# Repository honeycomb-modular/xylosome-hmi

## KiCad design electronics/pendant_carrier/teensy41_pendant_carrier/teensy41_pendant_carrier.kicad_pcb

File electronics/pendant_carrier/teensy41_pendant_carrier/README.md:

# Teensy 4.1 Pendant Carrier — KiCad project

A 2-layer carrier board that hosts a socketed Teensy 4.1 and breaks out two
pushbuttons and one Grayhill **62AG22-H5-P** optical encoder to JST-XH
connectors. The Teensy's own micro-USB carries data + power to a Raspberry Pi;
there is no power supply circuitry on the board. The encoder and buttons are
**not** mounted to this PCB — they wire in via ribbon/JST cables.

Complete KiCad **7** project. KiCad 8/9 will open it and offer a format
upgrade — expected and safe.

## This revision: board re-shaped to Sketch10.dxf

The board outline is now built **directly from your `Sketch10.dxf`** — the tall
pendant shape, ~48.7 x 89.3 mm, with the narrow body and the right-side bump,
all 8 filleted corners. The **4 mounting holes are at the exact DXF positions**
(2 on the body centreline, 2 in the bump).

Because the board went from a 95 mm-wide horizontal layout to this narrow
vertical one, everything was re-placed:

- **Teensy U1 is vertical**, in the long narrow body, **USB at the bottom**.
- **J1 / J2 / J3 are in the right-side bump** (the ribbon-cable area), vertical.
- **Passives** sit in the gap between the Teensy's two pin rows.
- Everything fits inside the outline and clears the mounting holes — verified.

## Opening it (close the old version first)

If the previous board is still open in KiCad, **close the project**, then open
`teensy41_pendant_carrier.kicad_pro`. **Just reload — do not run F8 / "Update PCB
from Schematic"** (everything is self-contained now; F8 is what pulled in the
oversized stock footprints last time).

In the PCB editor, press **`B`** to fill the GND-pour zones.

## Routing status

The board is now **fully routed** — all 8 nets are in copper:

- The **5 signal mains** (Teensy ↔ connector for BTN1, BTN2, ENC_A, ENC_B,
  ENC_SW) run on the top copper. To get them all crossing-free on one layer,
  J2 is placed above J1 — that ordering makes the connections monotonic.
- The **encoder pull-up / filter network** (R1, R2, C1, C2), the **debounce
  caps** (C3, C4), and the **power nets** (`+5V`, `+3V3`) route on the bottom
  copper, with **9 vias** dropping from the SMD passive pads to the bottom
  layer. The bottom copper is otherwise just the GND pour.
- **GND** is the pour on both layers — press `B` in the PCB editor to fill it.

I verified the whole thing with my own tooling: schematic netlist == PCB
netlist, **all 8 nets fully connected by copper**, every pad and via inside the
board outline, zero foreign-net crossings, zero trace-over-pad, zero via
clashes, zero trace-clearance violations, zero courtyard overlaps.

**KiCad's own DRC is still the authoritative check** — I built this without a
KiCad instance to test against, so run DRC once you've opened it (and `B` to
fill the zones first). If anything's off, the schematic is the known-good
source — *Tools → Update PCB from Schematic* re-flows it.

## Files

| File | What it is |
|---|---|
| `teensy41_pendant_carrier.kicad_pro` | Project file |
| `teensy41_pendant_carrier.kicad_sch` | Schematic — fully wired, all symbols embedded |
| `teensy41_pendant_carrier.kicad_pcb` | PCB — DXF outline, placed, 5 mains routed, GND zones |
| `teensy41_pendant_carrier.pretty/` | Project footprints: Teensy socket + both JST connectors |
| `fp-lib-table` / `sym-lib-table` | Library tables |
| `Sketch10.dxf` | Your enclosure outline (the source of the board shape) |
| `design-notes.md` | Full design document (part decode, BOM, firmware) |
| `schematic-diagram.svg` | Human-readable connection diagram |

R / C use the universal `Resistor_SMD` / `Capacitor_SMD` KiCad libraries; the
Teensy socket and JST connectors are project-local; mounting holes use the
stock `MountingHole` library.

## Netlist summary  (all routed in copper)

```
+5V     U1.VIN  J3.1  C5.1
+3V3    U1.3V3  R1.1  R2.1
GND     U1.GND  J3.4  J3.6  J1.2  J2.2  C1.2 C2.2 C3.2 C4.2 C5.2   (pour, both layers)
ENC_A   U1.D4   J3.2  R1.2  C1.1
ENC_B   U1.D5   J3.3  R2.2  C2.1
ENC_SW  U1.D6   J3.5
BTN1    U1.D2   J1.1  C3.1
BTN2    U1.D3   J2.1  C4.1
```

## Before fab

Sanity-check the Teensy footprint pin mapping against the official PJRC
pinout. The custom footprint is vertical with USB at the bottom; pads 1–24 are
the right column (digital pins), 25–48 the left column (power/analog). The
design taps pad 1 = GND, 4 = D2, 5 = D3, 6 = D4, 7 = D5, 8 = D6, 25 = VIN,
46 = 3V3.

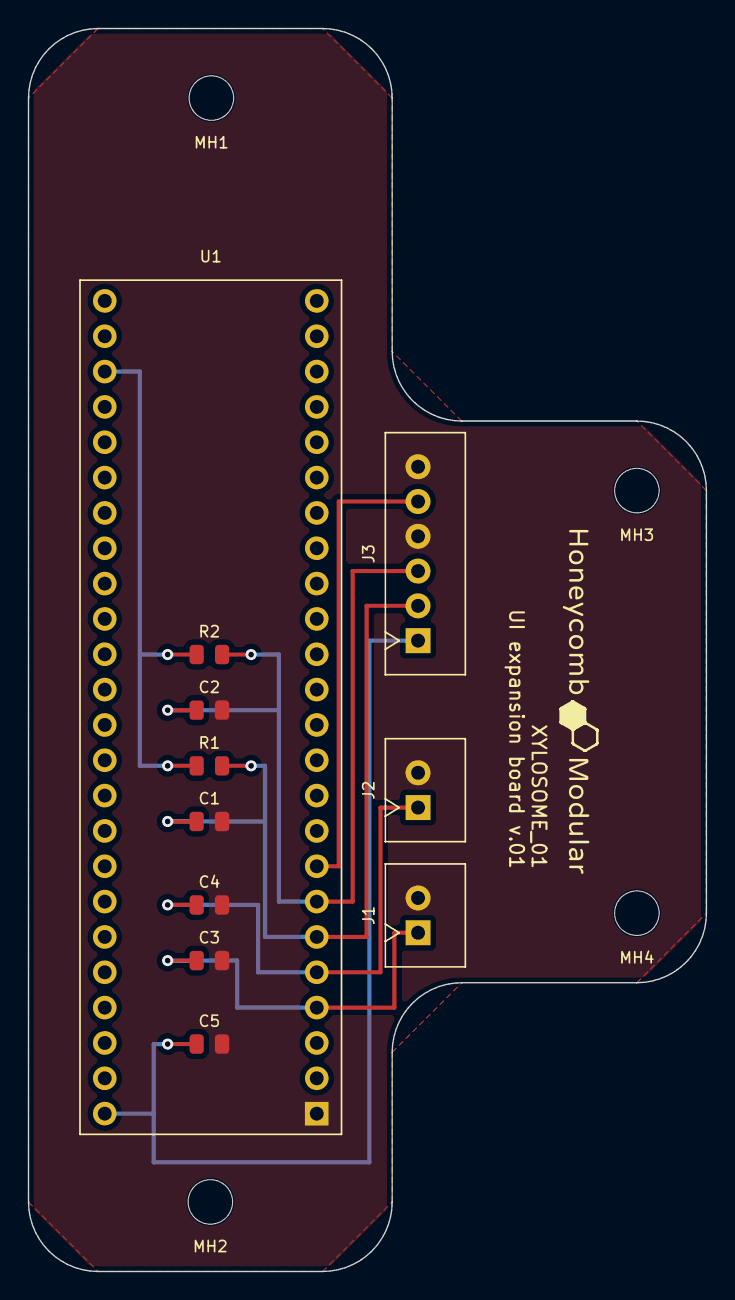
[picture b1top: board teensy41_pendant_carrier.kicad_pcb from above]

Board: 2 copper layers, 48.7 x 89.3 mm, 15 parts (0 on the bottom side), 8 nets.

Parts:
C1, C2: 470pF; C_0805_2012Metric
C3, C4: 100nF; C_0805_2012Metric
C5: 10uF; C_0805_2012Metric
J1: Button1; JST_XH_1x02_P2.50mm_Vertical
J2: Button2; JST_XH_1x02_P2.50mm_Vertical
J3: Encoder; JST_XH_1x06_P2.50mm_Vertical
MH1, MH2, MH3, MH4: MountingHole_3.2mm_M3
R1, R2: 10k; R_0805_2012Metric
U1: Teensy 4.1; Teensy4_1_Socketed_2x24

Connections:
+3V3: R1.1, R2.1, U1.46
+5V: C5.1, J3.1, U1.25
BTN1: C3.1, J1.1, U1.4
BTN2: C4.1, J2.1, U1.5
ENC_A: C1.1, J3.2, R1.2, U1.6
ENC_B: C2.1, J3.3, R2.2, U1.7
ENC_SW: J3.5, U1.8
GND: C1.2, C2.2, C3.2, C4.2, C5.2, J1.2, J2.2, J3.4, J3.6, U1.1

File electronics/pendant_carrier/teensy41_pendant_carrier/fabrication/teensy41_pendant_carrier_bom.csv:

"Id";"Designator";"Footprint";"Quantity";"Designation";"Supplier and ref";
1;"C1, C2";"C_0805_2012Metric";2;"470pF";;;
2;"C3, C4";"C_0805_2012Metric";2;"100nF";;;
3;"C5";"C_0805_2012Metric";1;"10uF";;;
4;"J1";"JST_XH_1x02_P2.50mm_Vertical";1;"Button1";;;
5;"J2";"JST_XH_1x02_P2.50mm_Vertical";1;"Button2";;;
6;"J3";"JST_XH_1x06_P2.50mm_Vertical";1;"Encoder";;;
7;"R1, R2";"R_0805_2012Metric";2;"10k";;;
8;"U1";"Teensy4_1_Socketed_2x24";1;"Teensy 4.1";;;

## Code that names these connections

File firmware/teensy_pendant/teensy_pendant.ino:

// teensy_pendant.ino - XYLOSOME pendant controller
// USB CDC serial to the Pi @ 115200. One ASCII line per event:
//   READY, BTN1 DOWN/UP, BTN2 DOWN/UP, ENC_SW DOWN/UP, JOG 1, JOG -1
//
// ENCODER DECODE — read this before "fixing" the jog feel:
//   The Grayhill 62AG22 (and the 61C11 test unit) have detents that are
//   mechanically OFFSET from their optical code by one position per cycle.
//   Per 4 clicks the raw quadrature reads:  clean(+1) clean(+1) DEAD(0) DOUBLE(+2).
//   The DEAD click makes no electrical change; the next click sweeps two states
//   (00->10->11) in <1 ms. This is a HARDWARE CHARACTERISTIC, not a wiring,
//   ground, solder, or board fault — all verified clean. See
//   electronics/.../WIRING.md "Encoder detent quirk". DO NOT re-troubleshoot it.
//
//   DECODE CHOICE (feel over count): emit exactly ONE step per detent landing.
//   The "double" detent is CAPPED to a single step (no 2-forward jump). The
//   paired "dead" detent still produces nothing (no signal exists for it). So
//   most clicks move one item; ~1 in 4 is a no-op. Absolute position can drift
//   over a long continuous spin — accepted, because menu nav wants an even
//   one-step-per-click feel, not exact position tracking.
#include <Bounce2.h>

static constexpr int PIN_BTN1   = 2;
static constexpr int PIN_BTN2   = 3;
static constexpr int PIN_ENC_A  = 4;
static constexpr int PIN_ENC_B  = 5;
static constexpr int PIN_ENC_SW = 6;

// Dwell (ms) after the last A/B change that marks the knob as "landed" on a
// detent. One JOG is emitted per landing. ~10-20 ms is imperceptible and well
// under the gap between tactile clicks.
static constexpr unsigned long SETTLE_MS = 15;

// Standard quadrature transition table, indexed by (prevAB << 2) | curAB.
static const int8_t QTAB[16] = { 0, 1, -1, 0,  -1, 0, 0, 1,
                                 1, 0, 0, -1,   0, -1, 1, 0 };

Bounce btn1, btn2, encSw;
static constexpr unsigned int DEBOUNCE_MS = 5;

static uint8_t prevAB = 0;
static long count = 0;        // running quadrature count (direction reference)
static long lastLanding = 0;  // count at the last settled detent
static elapsedMillis sinceChange;
static bool landed = true;

// (B,A) order so clockwise = +1. If rotation drives the UI the wrong way, swap
// PIN_ENC_B / PIN_ENC_A here.
static inline uint8_t readAB() {
    return (digitalRead(PIN_ENC_B) << 1) | digitalRead(PIN_ENC_A);
}

void setup() {
    Serial.begin(115200);
    btn1.attach(PIN_BTN1,    INPUT_PULLUP); btn1.interval(DEBOUNCE_MS);
    btn2.attach(PIN_BTN2,    INPUT_PULLUP); btn2.interval(DEBOUNCE_MS);
    encSw.attach(PIN_ENC_SW, INPUT_PULLUP); encSw.interval(DEBOUNCE_MS);
    pinMode(PIN_ENC_A, INPUT_PULLUP);
    pinMode(PIN_ENC_B, INPUT_PULLUP);
    prevAB = readAB();
    lastLanding = count;
    Serial.println("READY");
}

void loop() {
    btn1.update(); btn2.update(); encSw.update();
    if (btn1.fell())  Serial.println("BTN1 DOWN");
    if (btn1.rose())  Serial.println("BTN1 UP");
    if (btn2.fell())  Serial.println("BTN2 DOWN");
    if (btn2.rose())  Serial.println("BTN2 UP");
    if (encSw.fell()) Serial.println("ENC_SW DOWN");
    if (encSw.rose()) Serial.println("ENC_SW UP");

    uint8_t ab = readAB();
    if (ab != prevAB) {                 // moving — accumulate, reset dwell
        count += QTAB[(prevAB << 2) | ab];
        prevAB = ab;
        sinceChange = 0;
        landed = false;
    }
    else if (!landed && sinceChange >= SETTLE_MS) {
        landed = true;                  // settled on a detent
        if (count != lastLanding) {     // it moved -> ONE step, capped (no double)
            Serial.println(count > lastLanding ? "JOG 1" : "JOG -1");
            lastLanding = count;
        }
    }
}

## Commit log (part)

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2026-05-20 full project commit — xylosome_pi
2026-05-23 Pi 4: fullscreen QML scaling, kiosk boot config
2026-05-23 Pi 4: add Plymouth boot theme
2026-05-24 Pi: wire Teensy jog wheel to sequence box width
2026-05-24 Add metadata infuser spec
2026-05-25 feat: metadata infuser — trigger recorder + SVG export
2026-05-25 redesign SVG: XYLOSOME_01 header, two-line params, 200px height
2026-05-25 rename ScreenScan; restructure ScreenHome; update docs and notes; Pi4/Pi5 split documented
2026-05-25 add CLAUDE.md — Karpathy coding guidelines + xylosome context pointers
2026-05-25 Add ScreenCapture (jog/static/program modes), restructure ScreenHome nav
    - ScreenCapture.qml: three-tab capture mode screen
    - program scan: description + link back to ScreenScan
    - jog: position readout, slow/medium/fast speed selector, hold-to-jog buttons, enable/zero/capture
    - static: color (r/g/b/c 4-pass) or bw (single pass), capture button
    - ScreenHome: 5-row nav (capture modes, presets, connected devices, settings, metadata)
    - removed live row (absorbed into capture modes / jog)
2026-05-25 fix: uniform Theme colors throughout ScreenScan — all canvas greys and reds now reference Theme.colorTextDim / Theme.danger
2026-05-30 Add touch-free focus navigation across HMI + spline/dial encoder editing
2026-05-30 DEVLOG: 2026-05-29 focus nav session + dial blink-cursor note
2026-05-31 Build out menu hierarchy: settings submenu + sub-pages, presets/devices, reusable ChoiceList
    - ChoiceList: reusable titled, focus-navigable key=value screen with [back];
    option rows cycle on enter; rowActivated signal for special cases
    - settings is now a submenu -> network / camera / axis / calibration / display / system
    - six settings sub-pages with best-guess fields from the hardware spec
    - presets + connected devices are real pages (ScreenPresets, ScreenDevices)
    - strip titles/footers across sub-pages; bottom [back] in main-screen style
2026-05-31 Refine HMI: filled active chips, capture relayout, drop frame lines, inset spline focus
    - TerminalButton: active = solid accent FILL, focus = bright accent BORDER (orthogonal, no longer ambiguous)
    - ScreenCapture: jog/static panels regrouped into aligned label+control columns; jog pads paired
    - remove templatey header/footer hairlines from menus; keep only functional dividers; tighten contentTop
    - ScreenScan: focus frames the spline box (not the whole canvas/rainbow), tracks resize; brackets inset inside the box; grab-bar brightens at aspect level
    - FocusIndicator: bind to target geometry (follows live resize) + inset mode
2026-05-31 ScreenScan: aspect bar as its own section + triangle grip
    - aspect (green resize bar) is now a top-level focus section, sibling of the
    spline box and dial — not a sub-level
    - entering the spline box drops straight into scrub (removed the box level)
    - grey resize bar with an always-visible wedge: dark at rest, green when the
    bar is focused/slid; hairline gap on the left
    - focus brackets frame just the spline box (inset, tracks resize)
2026-06-01 WIP: Teensy PendantReader wiring (checkpoint before main merge)
2026-06-01 Rebuild main: latest UI + project; drop home-dir junk/secrets; add .gitignore; restore docs
2026-06-01 firmware: fix encoder direction + one-JOG-per-detent (61C11); add WIRING.md
2026-06-01 feat: PendantReader - Teensy serial drives UI focus nav via key events
2026-06-02 pendant: finalize position-correct encoder decoder; document 62AG detent quirk so it isn't re-troubleshot
2026-06-04 docs: fix eth0 dup-NM-profile lockout + AMOLED HDMI-A-1 display config
2026-06-05 Execute button: red/BTN1-only, pointer line, pendant grammar finalised
2026-06-07 Color/BW mode: Motor.colorMode, monochrome rainbow, indicator, ScreenCapture wired
2026-06-07 DEVLOG: 2026-06-05 session — ClearCore protocol + BW/Color mode
2026-06-07 QSettings persistence: scan state + presets; DEVLOG updated
2026-06-09 docs: Beckhoff EtherCAT architecture diagram
2026-06-09 docs: architecture diagram + PC setup note
2026-06-10 index on main: 5ebdecf feat: PendantReader - Teensy serial drives UI focus nav via key events
2026-06-10 beckhoff: build fixes + playhead follows real axis position
2026-06-10 smooth playhead: 25 Hz status + HMI interpolation
2026-06-10 xylod: log received commands
2026-06-10 hmi: gate playhead until first pass_start (no lead-in replay)
2026-06-10 beckhoff bench session: command logging, playhead smoothing + lead-in gate, devlog
2026-06-10 docs: camera/capture domain note — settings ownership, coupling rules, capture agent
2026-06-10 metadata: JSON sidecar per session (motosome verification) + export naming fix
2026-06-10 devlog: persistent bench — Pi NM dual address, xylod systemd service
2026-06-10 encoder: re-open detent-skip diagnosis — level-margin hypothesis + test plan
2026-06-10 encoder: document the three fix paths (firmware, VG swap, analog Schmitt, Rev C comparator)
2026-06-10 pendant: analog-decode firmware (Fix 2) — software Schmitt + built-in voltmeter
2026-06-10 encoder SOLVED: analog decode 1:1 — tuned thresholds, diagnosis results, supersede old verdict
2026-06-10 scan UI: kill local/daemon double-writer (root cause), quick pass reset, center-line = standard speed
2026-06-10 devlog: scan feel verified by artist
2026-06-10 capture: jog mode live against xylod — hold-pads, enable, home, real position, safety stops
2026-06-10 capture: dial-jog — encoder steps the axis (moveTo), pendant-native jog grammar
2026-06-10 devlog: jog mode verified by artist
2026-06-11 devlog: backlog — curve-semantics audit, boot leaning, pendant thermals
2026-06-11 suite: phase 0 — project skeleton, splash, CI matrix
2026-06-12 suite ci: macOS deployment target 12.0, universal binary
2026-06-12 suite: phase 2a — sessions, watch folder, file-pass pairing, sidecars, filmstrip, judging keys
2026-06-12 suite: phase 2b — libvips ingest (pyramids, previews, histograms), pairing drift guards, channel solo
2026-06-12 suite: phase 3 zoom viewer (tile streaming), pairing drift guards, filmstrip star row
2026-06-12 suite ci: fix glib/Qt signals macro collision, macOS arm64-only, vcpkg dir cache
2026-06-12 suite: vips C API (MSVC-linkable), Windows CI uses official libvips binaries
2026-06-12 suite ci: relocate libvips .pc prefixes on Windows
2026-06-12 suite ci: create include dirs the vips .pc references but doesn't ship
2026-06-12 suite ci: strip unresolvable -l entries from vips .pc, add link diagnostics
2026-06-12 suite ci: park Windows vips (judging-only artifact) pending msys2 toolchain
2026-06-12 devlog + suite handoff notes for next session
2026-06-12 ec_blink: visual EtherCAT bus proof (EL2008 LED chase); devlog: EK1100 bus bring-up verified
2026-06-12 ec_blink: fix build (cstdlib, Obytes/Ibytes)
2026-06-12 devlog: ec_blink verified on hardware — first process data on the real bus
2026-06-12 ec_meter: pendant-to-photon demo — live xylod position rendered on EL2008 LEDs
2026-06-12 ec_step: first EL7047 stepper spin, velocity-direct, 300 mA limit, all CoE indices doc-verified
2026-06-12 ec_step: phase-aware error handling + 0xA010 diag dump, abort only during motion
2026-06-12 devlog: first physical motion — ec_step spins Hanpose NEMA8 on EL7047; control-power vs motor-supply wiring facts recorded
2026-06-12 ec_dial: pendant dial drives the EL7047 stepper — xylod position follower with P velocity control
2026-06-12 ec_dial: tunable stiffness/velocity from CLI, crisp defaults (kp 30, 2 rev/s)
2026-06-12 ec_step: current argument (capped 1000 mA = Hanpose rating) + automatic speed range selection
2026-06-12 devlog: 20HT24 speed ladder measured (clean 8, dirty 12 rev/s); color-slide implications; ec_dial verified
2026-06-12 suite ci: Windows job on msys2/UCRT64 — native Qt6 + libvips, ingest enabled
2026-06-12 suite ci: relocate msys2 .pc prefixes to Windows paths
2026-06-12 suite: phase 4 — library grid/timeline, notes, permanent delete + quarantine, disk gauge, full mouse parity, zoom clip + 1600% cap
2026-06-12 suite ci: manual Qt deploy on msys2 (qt.conf + ldd DLL sweep)
2026-06-12 suite: archive importer (4b) + app icon (rainbow void)
2026-06-12 suite: archive importer (4b) + app icon (rainbow void, brightened)
2026-06-12 suite: metadata black/white variant per session, toggle via button, W key, menu
2026-06-13 A6-EC Er74.1 fix: enable DC SYNC0 at cycle time (motor_test + EcBackend); add full drive manual to docs
2026-06-13 motor_test: WKC + AL-state + SDO statusword diagnostics; wall-clock timeout fix
2026-06-13 motor_test: WKC/AL/SDO-statusword diagnostics, wall-clock timeout, INIT on exit
2026-06-13 motor_test: enforce+verify PRE-OP before PDO remap; name failing SDO with SOEM error text
2026-06-13 motor_test: DC phase-locked cyclic engine — gap-free frames through OP transition, PI alignment to DC time
2026-06-13 motor_test: read+write 0x1C32/0x1C33 sync config (DC-SYNC0 @ 1ms), activate SYNC0 before SAFE-OP like TwinCAT
2026-06-13 EcBackend: full A6-EC sync recipe (PRE-OP, 1C32/33, SYNC0-before-map, phase-locked in-thread OP), zero-at-wake, optional devices; conf: bench bus
2026-06-13 gear_ratio=50 (harmonic confirmed fitted); devlog: the curve ran on the real servo
2026-06-13 fast resets: return 240 deg/s output (2000 rpm motor), accel 1500 deg/s2
2026-06-13 docs: record verified imaging chain (Piranha HS-80-08K80 / Xcelera-CL PX4), fix CLHS->Camera Link; mark ClearCore architecture as stale fallback
2026-06-13 docs: add PROJECT_OVERVIEW.md as single source of truth; link from CLAUDE.md read-first list
2026-06-13 docs: Beckhoff network facts + real systemd auto-start; record the sim-drop-in 'won't turn from Pi' gotcha and fix
2026-06-14 docs: absolute-home path committed — StepperOnline AS7-C-ENC076-BAT battery encoder cable ordered; record bring-up steps
2026-06-16 xylod.conf: 2nd EL2008 added — bus positions shifted, drive 5->6 (fixes A6-EC PDO remap crash loop)
2026-06-16 docs: record 2026-06-16 fixes — EL2008 slave-shift (pos_drive 5->6) + netplan enp4s0 optional (boot-hang fix)
2026-06-16 docs: record drive boot-race fix (ExecStartPre sleep 15 drop-in) alongside slave-shift + netplan fixes
2026-06-17 docs: add panel_layout.svg + 4040 anodize bonding section (frame isn't one conductor; bonding star + verify)
2026-06-22 docs: add grabber_io_wiring.md — EL2521 RS-422 → Xtium-CL MX4 encoder/trigger pin map + Sapera params
2026-06-22 docs: add beep-test wire-ID method to grabber_io_wiring (find A/B + GND with a meter, label, tape off rest)
2026-06-23 docs: add cabinet_schematic.svg — stack layout + colour-coded connections (power/EtherCAT/network/motor/sync)
2026-06-23 notes: Pi read-only FS — keep HMI settings + exports on a writable partition so they persist
2026-06-27 xylod.conf: EL2521+EL5101 added — bus shifted, drive 6->8
2026-06-27 docs+conf: confirmed network topology (Pi static .2.3, switch-island lesson) + drive pos 6->8
2026-06-27 xylod: auto-locate A6-EC drive by product ID 0x715 (immune to terminal slave-shift)
2026-06-27 notes: battery encoder drive-side activated (C00.07=2, Er208 cleared)
2026-06-27 feat: absolute home — set_home command + persisted offset + HMI button
2026-06-27 xylod.conf: invert_axis=true — scan direction matches HMI sweep
2026-06-27 limits: symmetric +/-180 sweep around centered home
2026-06-28 xylod: shutdown button on EL1008 ch1 — 2s hold -> poweroff (+Pi via hook)
2026-06-28 hmi: curve top 300 deg/s + standard-speed setting + 1 deg/s floor
2026-06-28 xylod: dedicated jog accel (jog_acc_degs2=4000) for snappy dial-step jog
2026-06-28 hmi: lighten splash logo grey (85 -> 113)
2026-06-28 hmi: splash logo near-white (235) strokes on pure black
2026-06-29 shutdown button = single click (0.1s) + jog speeds [30,150,250]
2026-06-30 index on main: 6a82ed9 hmi: splash logo near-white (235) strokes on pure black
